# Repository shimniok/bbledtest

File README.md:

# bbledtest
Breadboard LED test array

An array of LEDs that can be plugged into a breadboard for testing or whatever else.

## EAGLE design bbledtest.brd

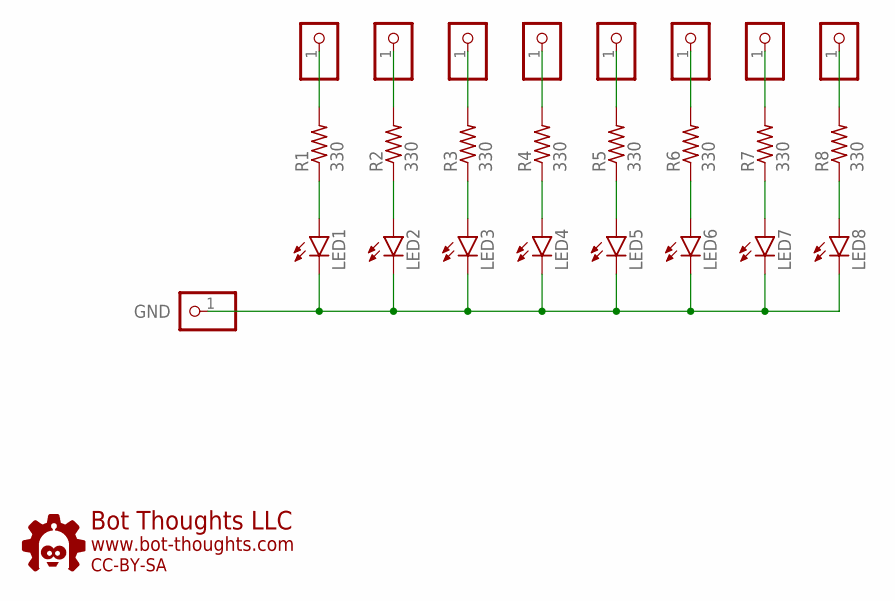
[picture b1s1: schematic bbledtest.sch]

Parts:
JP1, JP2, JP3, JP4, JP5, JP6, JP7, JP8: PINHD-1X01_2.54-S; 1X01-S
JP9: GND; 1X01-S
LED1, LED2, LED3, LED4, LED5, LED6, LED7, LED8: LEDCHIPLED_1206; CHIPLED_1206
R1, R2, R3, R4, R5, R6, R7, R8: 330; 0603
U$1: BTLOGO-LOGO-MD; BTLOGOM

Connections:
unnamed: LED5.A, R5.1
unnamed: LED4.A, R4.1
unnamed: LED3.A, R3.1
unnamed: LED2.A, R2.1
unnamed: LED1.A, R1.1
unnamed: LED7.A, R7.1
unnamed: LED6.A, R6.1
unnamed: LED8.A, R8.1
unnamed: JP1.1, R1.2
unnamed: JP2.1, R2.2
unnamed: JP3.1, R3.2
unnamed: JP4.1, R4.2
unnamed: JP6.1, R6.2
unnamed: JP7.1, R7.2
unnamed: JP5.1, R5.2
unnamed: JP8.1, R8.2
unnamed: JP9.1, LED1.C, LED2.C, LED3.C, LED4.C, LED5.C, LED6.C, LED7.C, LED8.C

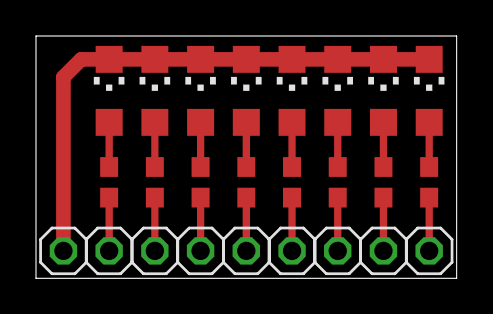
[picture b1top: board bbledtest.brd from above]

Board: 2 copper layers, 23.4 x 13.5 mm, 26 parts (1 on the bottom side), 17 nets.

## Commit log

2017-03-18 inital version as ordered
2021-02-10 added description

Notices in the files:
bbledtest.brd:
CC-BY-SA
